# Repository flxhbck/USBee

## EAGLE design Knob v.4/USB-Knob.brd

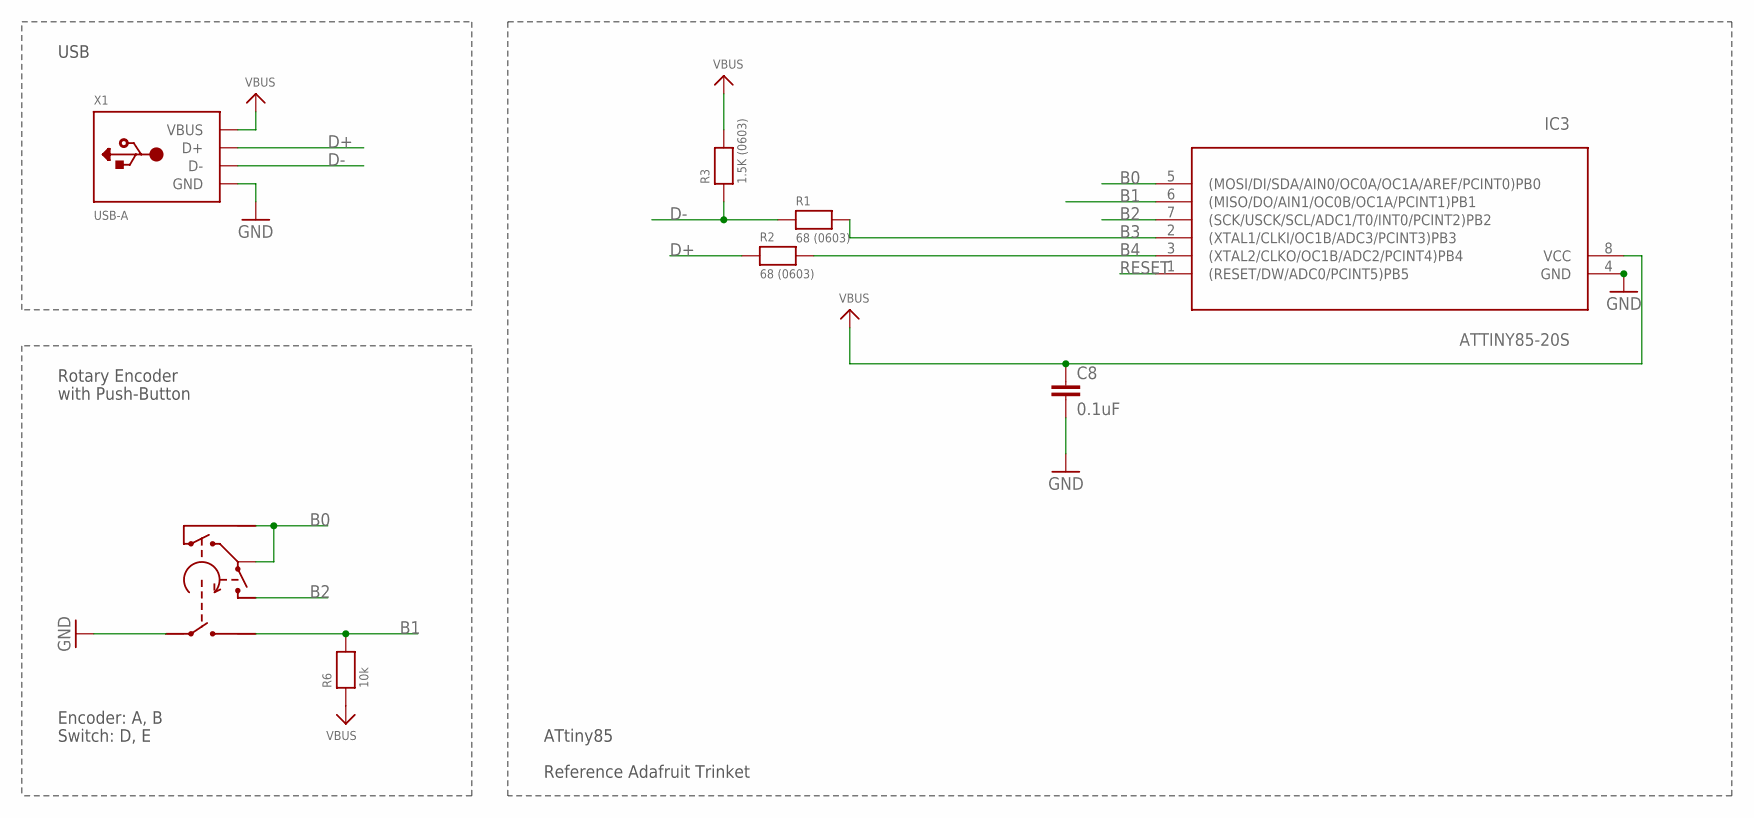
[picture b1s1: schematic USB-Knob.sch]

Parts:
C8: 0.1uF; 0603-CAP
IC3: ATTINY85-20S; SOIC8
R1, R2: 68 (0603); 0603-NO
R3: 1.5K (0603); 0603-NO
R6: 10k; 0603-NO
U$1: EVE-S
X1: USB-A; MOLEX_480371000

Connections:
B0: IC3.5 ((MOSI/DI/SDA/AIN0/OC0A/OC1A/AREF/PCINT0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), U$1.1 (A), U$1.GND0 (COM), U$1.GND1 (COM), U$1.GND2 (COM)
B1: IC3.6 ((MISO/DO/AIN1/OC0B/OC1A/PCINT1)PB1), R6.2, U$1.B2 (S2)
B2: IC3.7 ((SCK/USCK/SCL/ADC1/T0/INT0/PCINT2)PB2), U$1.2 (B)
B3: IC3.2 ((XTAL1/CLKI/OC1B/ADC3/PCINT3)PB3), R1.2
B4: IC3.3 ((XTAL2/CLKO/OC1B/ADC2/PCINT4)PB4), R2.2
D+: R2.1, X1.3 (D+)
D-: R1.1, R3.1, X1.2 (D-)
GND: C8.2, IC3.4 (GND), U$1.B1 (S1), X1.4 (GND)
RESET: IC3.1 ((RESET/DW/ADC0/PCINT5)PB5)
VBUS: C8.1, IC3.8 (VCC), R3.2, R6.1, X1.1 (VBUS)

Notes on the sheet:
Rotary Encoder
USB
ATtiny85
Reference Adafruit Trinket
with Push-Button
Encoder: A, B
Switch: D, E

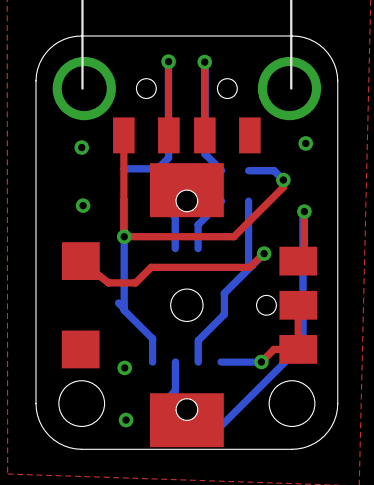
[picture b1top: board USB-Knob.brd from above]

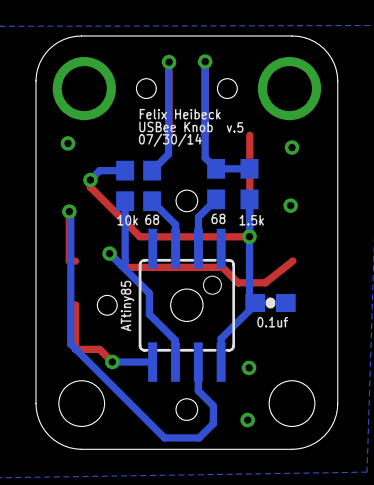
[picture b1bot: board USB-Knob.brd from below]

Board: 2 copper layers, 16.8 x 23.0 mm, 8 parts (6 on the bottom side), 9 nets.

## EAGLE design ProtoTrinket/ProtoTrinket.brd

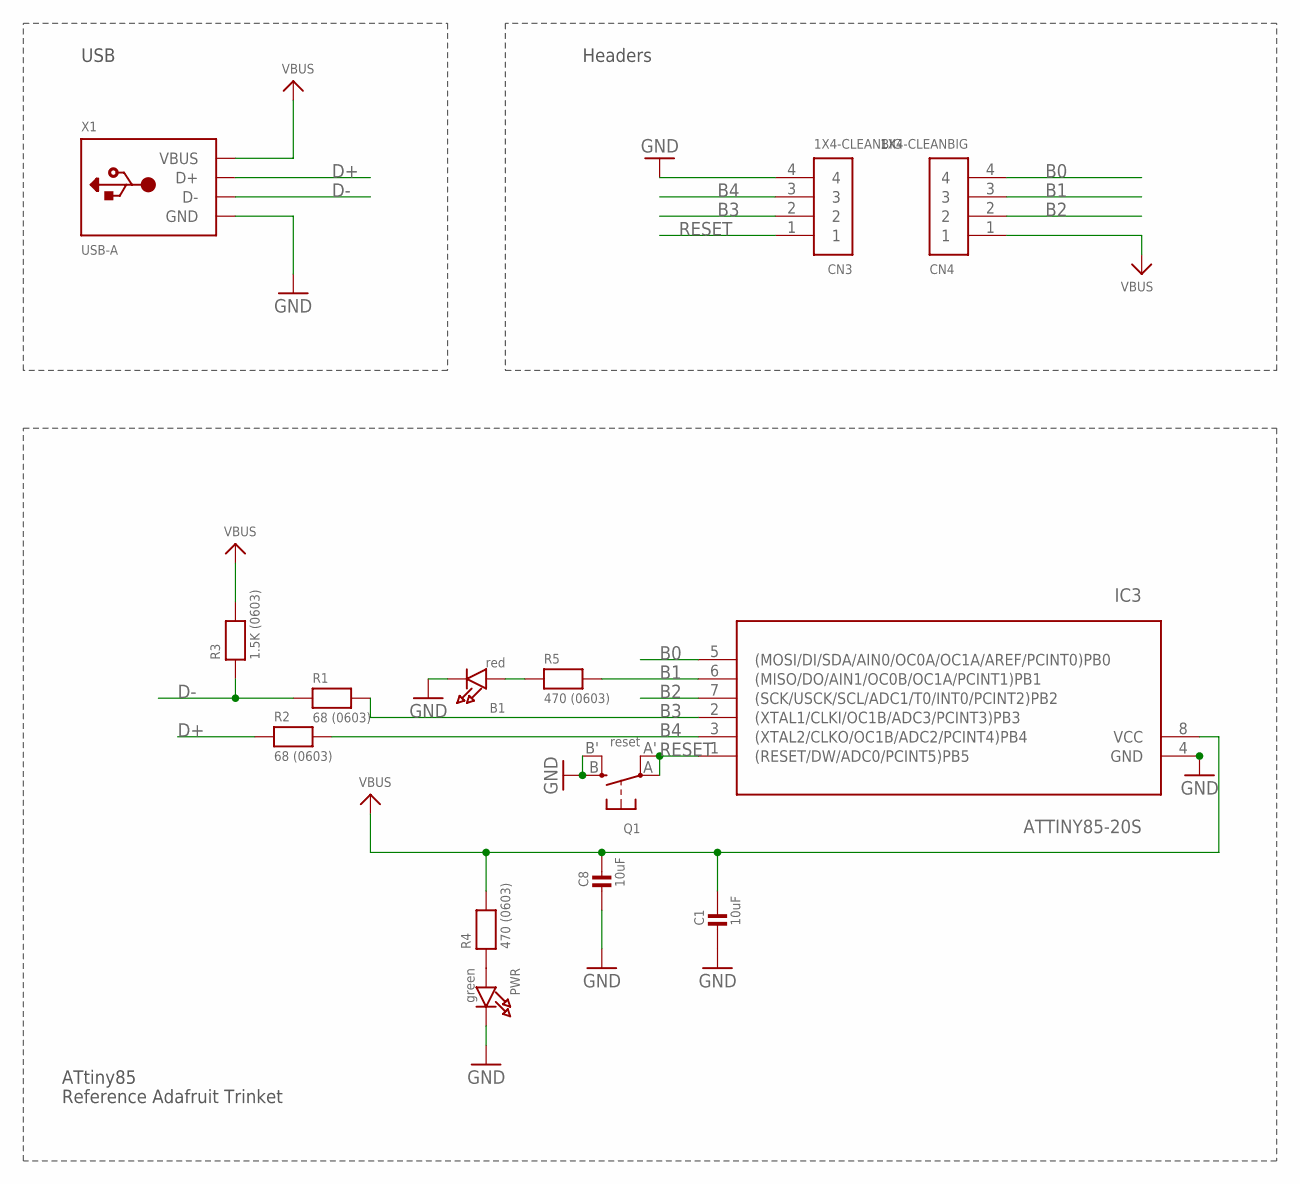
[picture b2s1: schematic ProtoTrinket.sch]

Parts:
B1: red; CHIPLED_0805_NOOUTLINE
C1, C8: 10uF; 0805-NO
CN3, CN4: 1X4-CLEANBIG; 1X04-CLEANBIG
IC3: ATTINY85-20S; SOIC8
PWR: green; CHIPLED_0805_NOOUTLINE
Q1: reset; BTN_KMR2_4.6X2.8
R1, R2: 68 (0603); 0603-NO
R3: 1.5K (0603); 0603-NO
R4, R5: 470 (0603); 0603-NO
X1: USB-A; MOLEX_480371000

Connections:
B0: CN4.4, IC3.5 ((MOSI/DI/SDA/AIN0/OC0A/OC1A/AREF/PCINT0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)
B1: CN4.3, IC3.6 ((MISO/DO/AIN1/OC0B/OC1A/PCINT1)PB1), R5.2
B2: CN4.2, IC3.7 ((SCK/USCK/SCL/ADC1/T0/INT0/PCINT2)PB2)
B3: CN3.2, IC3.2 ((XTAL1/CLKI/OC1B/ADC3/PCINT3)PB3), R1.2
B4: CN3.3, IC3.3 ((XTAL2/CLKO/OC1B/ADC2/PCINT4)PB4), R2.2
D+: R2.1, X1.3 (D+)
D-: R1.1, R3.1, X1.2 (D-)
GND: B1.C, C1.2, C8.2, CN3.4, IC3.4 (GND), PWR.C, Q1.B (S), Q1.B' (S1), X1.4 (GND)
unnamed: B1.A, R5.1
unnamed: PWR.A, R4.1
RESET: CN3.1, IC3.1 ((RESET/DW/ADC0/PCINT5)PB5), Q1.A, Q1.A' (P1)
VBUS: C1.1, C8.1, CN4.1, IC3.8 (VCC), R3.2, R4.2, X1.1 (VBUS)

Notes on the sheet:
USB
Headers
ATtiny85
Reference Adafruit Trinket

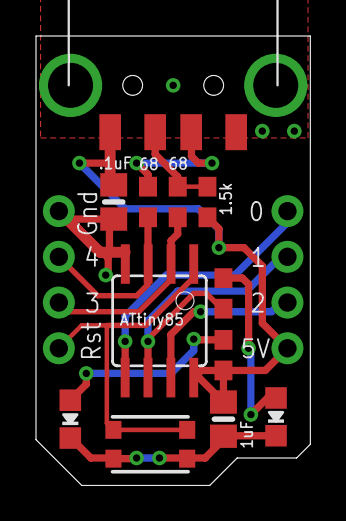
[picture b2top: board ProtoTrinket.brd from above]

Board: 2 copper layers, 15.2 x 25.0 mm, 14 parts (0 on the bottom side), 12 nets.

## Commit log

2015-03-12 init
2015-03-30 knob-code
    added code for volume knob.
    also arrow-key variation.
2015-04-07 added SMD version of Knob
2016-02-07 add v.3 & v.4

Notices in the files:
parts and their libraries:
microbuilder: This work is placed in the public domain, and may be freely used for commercial and non-commercial work with the following conditions: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
SparkFun-Capacitors: Licensing: Creative Commons ShareAlike 4.0 International - https://creativecommons.org/licenses/by-sa/4.0
